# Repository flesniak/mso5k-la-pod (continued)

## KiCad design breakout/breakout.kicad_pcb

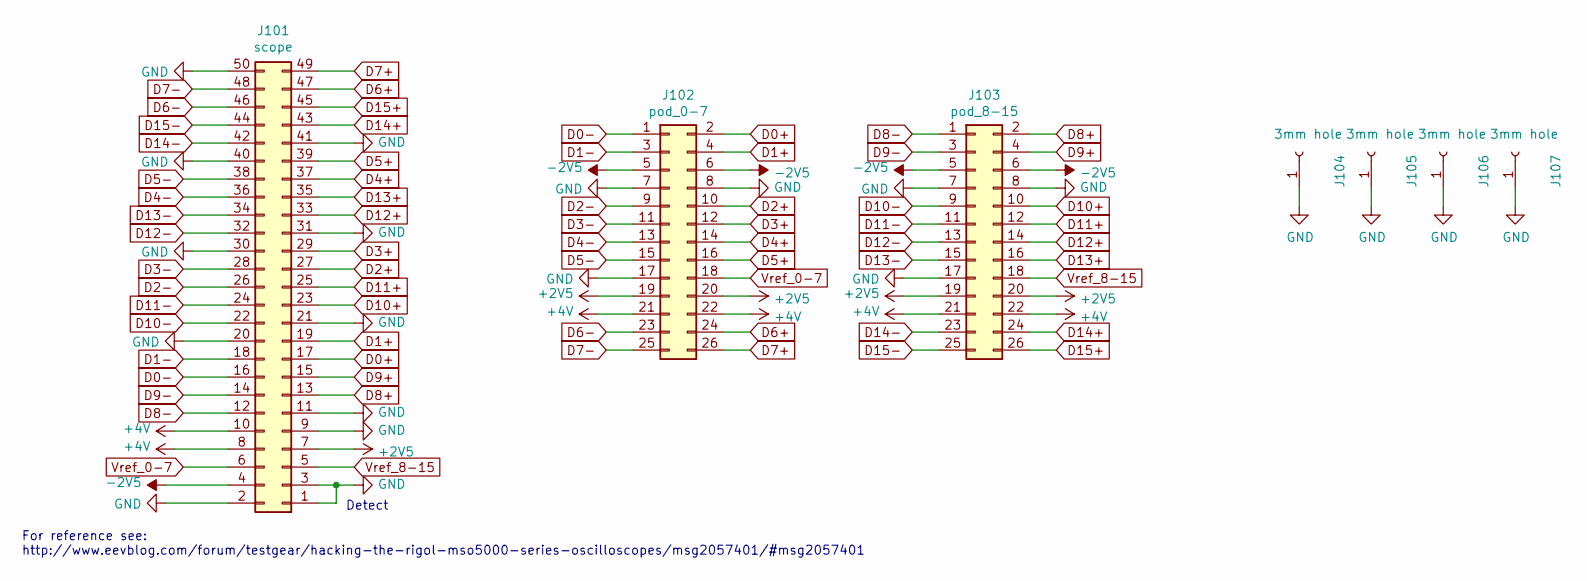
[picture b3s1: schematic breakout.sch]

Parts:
J101: scope; PinHeader_2x25_P2.54mm_Vertical
J102: pod_0-7; PinHeader_2x13_P1.27mm_Vertical_SMD
J103: pod_8-15; PinHeader_2x13_P1.27mm_Vertical_SMD
J104, J105, J106, J107: 3mm hole; 3mm

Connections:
+2V5: J101.7, J102.19, J102.20, J103.19, J103.20
+4V: J101.8, J101.10, J102.21, J102.22, J103.21, J103.22
-2V5: J101.4, J102.5, J102.6, J103.5, J103.6
D0+: J101.17, J102.2
D0-: J101.16, J102.1
D1+: J101.19, J102.4
D1-: J101.18, J102.3
D2+: J101.27, J102.10
D2-: J101.26, J102.9
D3+: J101.29, J102.12
D3-: J101.28, J102.11
D4+: J101.37, J102.14
D4-: J101.36, J102.13
D5+: J101.39, J102.16
D5-: J101.38, J102.15
D6+: J101.47, J102.24
D6-: J101.46, J102.23
D7+: J101.49, J102.26
D7-: J101.48, J102.25
D8+: J101.13, J103.2
D8-: J101.12, J103.1
D9+: J101.15, J103.4
D9-: J101.14, J103.3
D10+: J101.23, J103.10
D10-: J101.22, J103.9
D11+: J101.25, J103.12
D11-: J101.24, J103.11
D12+: J101.33, J103.14
D12-: J101.32, J103.13
D13+: J101.35, J103.16
D13-: J101.34, J103.15
D14+: J101.43, J103.24
D14-: J101.42, J103.23
D15+: J101.45, J103.26
D15-: J101.44, J103.25
GND: J101.1, J101.2, J101.3, J101.9, J101.11, J101.20, J101.21, J101.30, J101.31, J101.40, J101.41, J101.50, J102.7, J102.8, J102.17, J103.7, J103.8, J103.17, J104.1, J105.1, J106.1, J107.1
Vref_0-7: J101.6, J102.18
Vref_8-15: J101.5, J103.18

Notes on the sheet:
For reference see: http://www.eevblog.com/forum/testgear/hacking-the-rigol-mso5000-series-oscilloscopes/msg2057401/#msg2057401
Detect

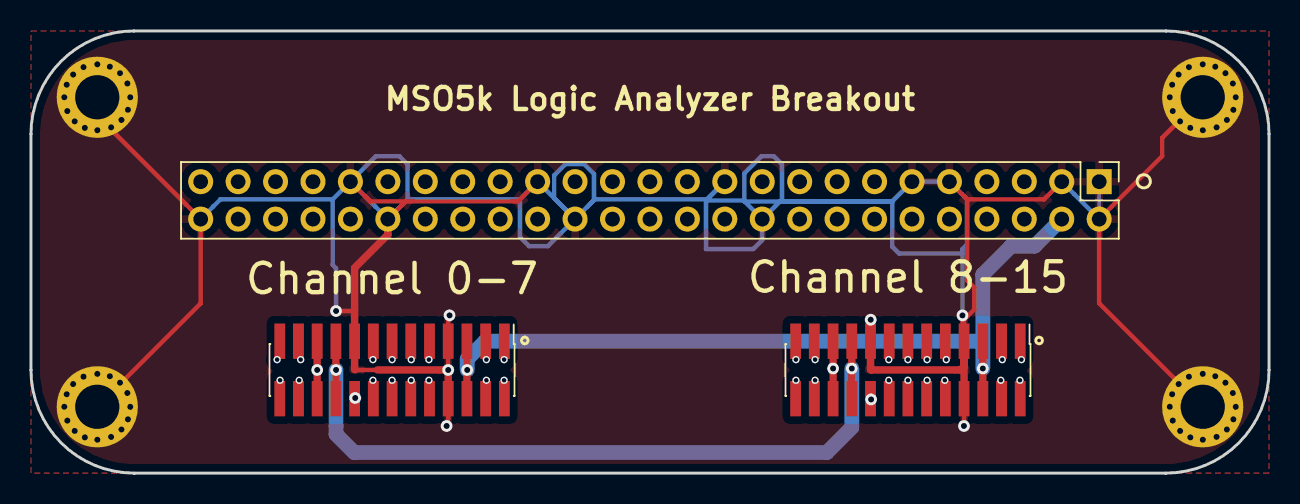
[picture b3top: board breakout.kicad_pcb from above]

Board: 4 copper layers, 84.0 x 30.0 mm, 7 parts (0 on the bottom side), 38 nets.

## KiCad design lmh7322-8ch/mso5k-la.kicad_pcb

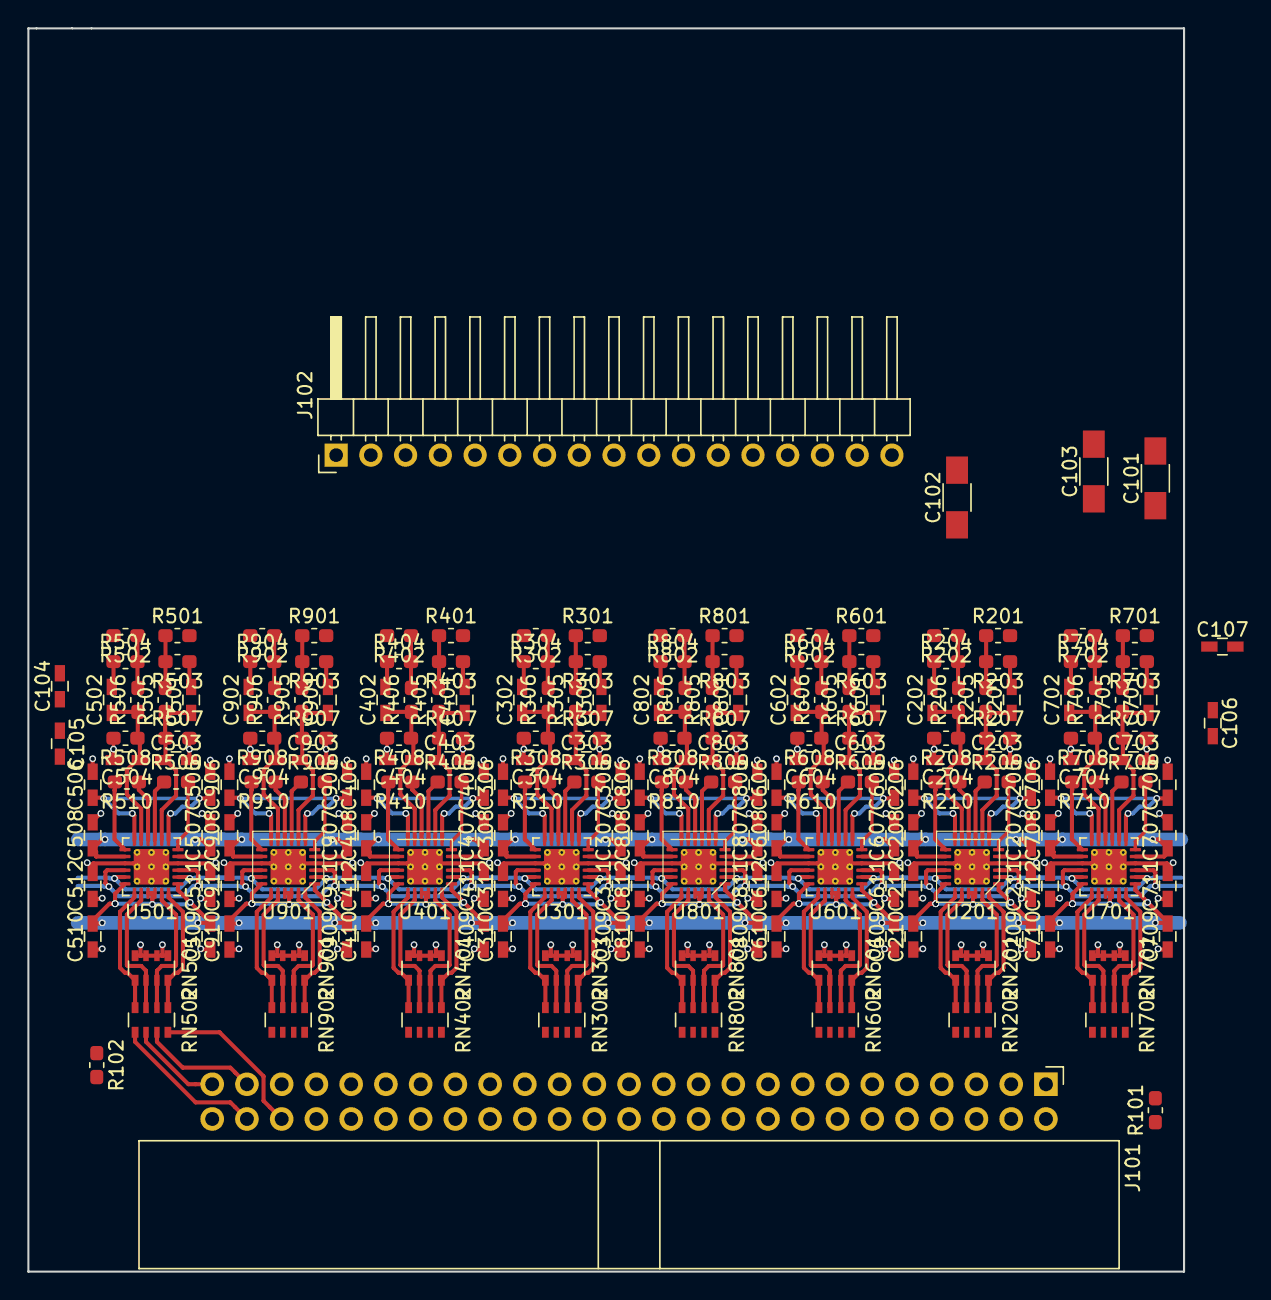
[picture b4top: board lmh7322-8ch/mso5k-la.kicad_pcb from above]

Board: 4 copper layers, 84.5 x 90.9 mm, 211 parts (0 on the bottom side), 168 nets.

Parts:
C101, C102, C103: 10uF; C_1206_HandSoldering
C104, C105, C106, C107, C207, C208, C209, C210, C211, C212, C307, C308, C309, C310, C311, C312, C407, C408, C409, C410, C411, C412, C507, C508, C509, C510, C511, C512, C607, C608, C609, C610, C611, C612, C707, C708, C709, C710, C711, C712, C807, C808, C809, C810, C811, C812, C907, C908, C909, C910, C911, C912: 100n; C_0603_HandSoldering
C201, C202, C301, C302, C401, C402, C501, C502, C601, C602, C701, C702, C801, C802, C901, C902: 3.3p; C_0603_HandSoldering
C203, C204, C303, C304, C403, C404, C503, C504, C603, C604, C703, C704, C803, C804, C903, C904: 27p; C_0603_HandSoldering
C205, C206, C305, C306, C405, C406, C505, C506, C605, C606, C705, C706, C805, C806, C905, C906: 10n; C_0603_HandSoldering
J101: output; IDC-Header_2x25_Pitch2.54mm_Angled
J102: input; PinHeader_1x17_P2.54mm_Horizontal
R101, R102: 1k; R_0603_1608Metric_Pad1.05x0.95mm_HandSolder
R201, R202, R301, R302, R401, R402, R501, R502, R601, R602, R701, R702, R801, R802, R901, R902: 300; R_0603_1608Metric_Pad1.05x0.95mm_HandSolder
R203, R204, R303, R304, R403, R404, R503, R504, R603, R604, R703, R704, R803, R804, R903, R904: 497; R_0603_1608Metric_Pad1.05x0.95mm_HandSolder
R205, R206, R305, R306, R405, R406, R505, R506, R605, R606, R705, R706, R805, R806, R905, R906: 90k8; R_0603_1608Metric_Pad1.05x0.95mm_HandSolder
R207, R208, R209, R210, R307, R308, R309, R310, R407, R408, R409, R410, R507, R508, R509, R510, R607, R608, R609, R610, R707, R708, R709, R710, R807, R808, R809, R810, R907, R908, R909, R910: 10k; R_0603_1608Metric_Pad1.05x0.95mm_HandSolder
RN201, RN301, RN401, RN501, RN601, RN701, RN801, RN901: 220; R_Array_Convex_4x0603
RN202, RN302, RN402, RN502, RN602, RN702, RN802, RN902: 49R9; R_Array_Convex_4x0603
U201, U301, U401, U501, U601, U701, U801, U901: lmh7322; QFN-24-1EP_4x4mm_P0.5mm_EP2.6x2.6mm_ThermalVias

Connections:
+2V5: C102.1, C209.2, C210.2, C309.2, C310.2, C409.2, C410.2, C509.2, C510.2, C609.2, C610.2, C709.2, C710.2, C809.2, C810.2, C909.2, C910.2, J101.7, R101.1, U201.1, U201.18, U201.21, U201.22, U301.1, U301.18, U301.21, U301.22, U401.1, U401.18, U401.21, U401.22, U501.1, U501.18, U501.21, U501.22, U601.1, U601.18, U601.21, U601.22, U701.1, U701.18, U701.21, U701.22, U801.1, U801.18, U801.21, U801.22, U901.1, U901.18, U901.21, U901.22
+4V: C101.1, C207.1, C208.1, C307.1, C308.1, C407.1, C408.1, C507.1, C508.1, C607.1, C608.1, C707.1, C708.1, C807.1, C808.1, C907.1, C908.1, J101.8, J101.10, U201.5, U201.14, U301.5, U301.14, U401.5, U401.14, U501.5, U501.14, U601.5, U601.14, U701.5, U701.14, U801.5, U801.14, U901.5, U901.14
-2V5: C103.1, C211.2, C212.2, C311.2, C312.2, C411.2, C412.2, C511.2, C512.2, C611.2, C612.2, C711.2, C712.2, C811.2, C812.2, C911.2, C912.2, J101.4, R102.1, U201.4, U201.15, U201.25, U301.4, U301.15, U301.25, U401.4, U401.15, U401.25, U501.4, U501.15, U501.25, U601.4, U601.15, U601.25, U701.4, U701.15, U701.25, U801.4, U801.15, U801.25, U901.4, U901.15, U901.25
D0: J101.17, RN202.7
D1: J101.19, RN202.6
D2: J101.27, RN302.7
D3: J101.29, RN302.6
D4: J101.37, RN402.7
D5: J101.39, RN402.6
D6: J101.47, RN502.7
D7: J101.49, RN502.6
D8: J101.13, RN702.7
D9: J101.15, RN702.6
D10: J101.23, RN602.7
D11: J101.25, RN602.6
D12: J101.33, RN802.7
D13: J101.35, RN802.6
D14: J101.43, RN902.7
D15: J101.45, RN902.6
GND: C101.2, C102.2, C103.2, C104.2, C105.2, C106.2, C107.2, C203.2, C204.2, C205.2, C206.2, C207.2, C208.2, C209.1, C210.1, C211.1, C212.1, C303.2, C304.2, C305.2, C306.2, C307.2, C308.2, C309.1, C310.1, C311.1, C312.1, C403.2, C404.2, C405.2, C406.2, C407.2, C408.2, C409.1, C410.1, C411.1, C412.1, C503.2, C504.2, C505.2, C506.2, C507.2, C508.2, C509.1, C510.1, C511.1, C512.1, C603.2, C604.2, C605.2, C606.2, C607.2, C608.2, C609.1, C610.1, C611.1, C612.1, C703.2, C704.2, C705.2, C706.2, C707.2, C708.2, C709.1, C710.1, C711.1, C712.1, C803.2, C804.2, C805.2, C806.2, C807.2, C808.2, C809.1, C810.1, C811.1, C812.1, C903.2, C904.2, C905.2, C906.2, C907.2, C908.2, C909.1, C910.1, C911.1, C912.1, J101.1, J101.2, J101.3, J101.9, J101.11, J101.20, J101.21, J101.30, J101.31, J101.40, J101.41, J101.50, J102.9, R207.2, R208.2, R307.2, R308.2, R407.2, R408.2, R507.2, R508.2, R607.2, R608.2, R707.2, R708.2, R807.2, R808.2, R907.2, R908.2, RN201.1, RN201.2, RN201.3, RN201.4, RN301.1, RN301.2, RN301.3, RN301.4, RN401.1, RN401.2, RN401.3, RN401.4, RN501.1, RN501.2, RN501.3, RN501.4, RN601.1, RN601.2, RN601.3, RN601.4, RN701.1, RN701.2, RN701.3, RN701.4, RN801.1, RN801.2, RN801.3, RN801.4, RN901.1, RN901.2, RN901.3, RN901.4
In0: J102.1, R201.2
In1: J102.2, R202.2
In2: J102.3, R301.2
In3: J102.4, R302.2
In4: J102.5, R401.2
In5: J102.6, R402.2
In6: J102.7, R501.2
In7: J102.8, R502.2
In8: J102.10, R701.2
In9: J102.11, R702.2
In10: J102.12, R601.2
In11: J102.13, R602.2
In12: J102.14, R801.2
In13: J102.15, R802.2
In14: J102.16, R901.2
In15: J102.17, R902.2
LE: R102.2, U201.2, U201.17, U301.2, U301.17, U401.2, U401.17, U501.2, U501.17, U601.2, U601.17, U701.2, U701.17, U801.2, U801.17, U901.2, U901.17
unnamed: C201.1, C203.1, R205.1, R207.1, U201.8
unnamed: C201.2, R203.1
unnamed: C202.1, C204.1, R206.1, R208.1, U201.11
unnamed: C202.2, R204.1
unnamed: C301.1, C303.1, R305.1, R307.1, U301.8
unnamed: C301.2, R303.1
unnamed: C302.1, C304.1, R306.1, R308.1, U301.11
unnamed: C302.2, R304.1
unnamed: C401.1, C403.1, R405.1, R407.1, U401.8
unnamed: C401.2, R403.1
unnamed: C402.1, C404.1, R406.1, R408.1, U401.11
unnamed: C402.2, R404.1
unnamed: C501.1, C503.1, R505.1, R507.1, U501.8
unnamed: C501.2, R503.1
unnamed: C502.1, C504.1, R506.1, R508.1, U501.11
unnamed: C502.2, R504.1
unnamed: C601.1, C603.1, R605.1, R607.1, U601.8
unnamed: C601.2, R603.1
unnamed: C602.1, C604.1, R606.1, R608.1, U601.11
unnamed: C602.2, R604.1
unnamed: C701.1, C703.1, R705.1, R707.1, U701.8
unnamed: C701.2, R703.1
unnamed: C702.1, C704.1, R706.1, R708.1, U701.11
unnamed: C702.2, R704.1
unnamed: C801.1, C803.1, R805.1, R807.1, U801.8
unnamed: C801.2, R803.1
unnamed: C802.1, C804.1, R806.1, R808.1, U801.11
unnamed: C802.2, R804.1
unnamed: C901.1, C903.1, R905.1, R907.1, U901.8
unnamed: C901.2, R903.1
unnamed: C902.1, C904.1, R906.1, R908.1, U901.11
unnamed: C902.2, R904.1
unnamed: R201.1, R203.2, R205.2
unnamed: R202.1, R204.2, R206.2
unnamed: R209.1, U201.9
unnamed: R209.2, U201.6
unnamed: R210.1, U201.10
unnamed: R210.2, U201.13
unnamed: R301.1, R303.2, R305.2
unnamed: R302.1, R304.2, R306.2
unnamed: R309.1, U301.9
unnamed: R309.2, U301.6
unnamed: R310.1, U301.10
unnamed: R310.2, U301.13
unnamed: R401.1, R403.2, R405.2
unnamed: R402.1, R404.2, R406.2
unnamed: R409.1, U401.9
unnamed: R409.2, U401.6
unnamed: R410.1, U401.10
unnamed: R410.2, U401.13
unnamed: R501.1, R503.2, R505.2
unnamed: R502.1, R504.2, R506.2
unnamed: R509.1, U501.9
unnamed: R509.2, U501.6
unnamed: R510.1, U501.10
unnamed: R510.2, U501.13
unnamed: R601.1, R603.2, R605.2
unnamed: R602.1, R604.2, R606.2
unnamed: R609.1, U601.9
unnamed: R609.2, U601.6
unnamed: R610.1, U601.10
unnamed: R610.2, U601.13
unnamed: R701.1, R703.2, R705.2
unnamed: R702.1, R704.2, R706.2
unnamed: R709.1, U701.9
unnamed: R709.2, U701.6
unnamed: R710.1, U701.10
unnamed: R710.2, U701.13
unnamed: R801.1, R803.2, R805.2
unnamed: R802.1, R804.2, R806.2
unnamed: R809.1, U801.9
unnamed: R809.2, U801.6
unnamed: R810.1, U801.10
unnamed: R810.2, U801.13
unnamed: R901.1, R903.2, R905.2
unnamed: R902.1, R904.2, R906.2
unnamed: R909.1, U901.9
unnamed: R909.2, U901.6
unnamed: R910.1, U901.10
unnamed: R910.2, U901.13
unnamed: RN201.5, RN202.4, U201.19
unnamed: RN201.6, RN202.3, U201.20
unnamed: RN201.7, RN202.2, U201.23
unnamed: RN201.8, RN202.1, U201.24
unnamed: RN301.5, RN302.4, U301.19
unnamed: RN301.6, RN302.3, U301.20
unnamed: RN301.7, RN302.2, U301.23
unnamed: RN301.8, RN302.1, U301.24
unnamed: RN401.5, RN402.4, U401.19
unnamed: RN401.6, RN402.3, U401.20
unnamed: RN401.7, RN402.2, U401.23
unnamed: RN401.8, RN402.1, U401.24
unnamed: RN501.5, RN502.4, U501.19
unnamed: RN501.6, RN502.3, U501.20
unnamed: RN501.7, RN502.2, U501.23
unnamed: RN501.8, RN502.1, U501.24
unnamed: RN601.5, RN602.4, U601.19
unnamed: RN601.6, RN602.3, U601.20
unnamed: RN601.7, RN602.2, U601.23
unnamed: RN601.8, RN602.1, U601.24
unnamed: RN701.5, RN702.4, U701.19
unnamed: RN701.6, RN702.3, U701.20
unnamed: RN701.7, RN702.2, U701.23
unnamed: RN701.8, RN702.1, U701.24
unnamed: RN801.5, RN802.4, U801.19
unnamed: RN801.6, RN802.3, U801.20
unnamed: RN801.7, RN802.2, U801.23
unnamed: RN801.8, RN802.1, U801.24
unnamed: RN901.5, RN902.4, U901.19
unnamed: RN901.6, RN902.3, U901.20
unnamed: RN901.7, RN902.2, U901.23
unnamed: RN901.8, RN902.1, U901.24
Vref_0-7: C104.1, C106.1, C205.1, C206.1, C305.1, C306.1, C405.1, C406.1, C505.1, C506.1, J101.6, U201.7, U201.12, U301.7, U301.12, U401.7, U401.12, U501.7, U501.12
Vref_8-15: C105.1, C107.1, C605.1, C606.1, C705.1, C706.1, C805.1, C806.1, C905.1, C906.1, J101.5, U601.7, U601.12, U701.7, U701.12, U801.7, U801.12, U901.7, U901.12
~D0: J101.16, RN202.8
~D1: J101.18, RN202.5
~D2: J101.26, RN302.8
~D3: J101.28, RN302.5
~D4: J101.36, RN402.8
~D5: J101.38, RN402.5
~D6: J101.46, RN502.8
~D7: J101.48, RN502.5
~D8: J101.12, RN702.8
~D9: J101.14, RN702.5
~D10: J101.22, RN602.8
~D11: J101.24, RN602.5
~D12: J101.32, RN802.8
~D13: J101.34, RN802.5
~D14: J101.42, RN902.8
~D15: J101.44, RN902.5
~LE: R101.2, U201.3, U201.16, U301.3, U301.16, U401.3, U401.16, U501.3, U501.16, U601.3, U601.16, U701.3, U701.16, U801.3, U801.16, U901.3, U901.16

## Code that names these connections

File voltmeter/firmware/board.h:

#pragma once

#include "avr8gpio.h"

/*
| Define         | AVR | Pin | Description |
|----------------|-----|-----|-------------|
| LED0           | PA0 | 13  | LED0        |
| LED1           | PA1 | 12  | LED1        |
| LED2           | PA2 | 11  | LED2        |
| LED3           | PA3 | 10  | LED3        |
| LED4           | PB0 | 2   | LED3        |
| CALIB          | PA6 | 7   | Calibration |
| VREF0          | PA5 | 8   | VrefA       |
| VREF1          | PA7 | 6   | VrefB       |
|                | PB3 | 4   | Reset       |
*/

#define LED0  GPA0
#define LED1  GPA1
#define LED2  GPA2
#define LED3  GPA3
#define LED4  GPB0
#define CALIB GPA6

#define VREF0 GPA5
#define VREF1 GPA7
#define VREF0_ADC 5
#define VREF1_ADC 7

//#define SOFTWARE_TX GPB0

// pullup for calibration input
#define DEFAULT_PORTA (_BV(PA6))

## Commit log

2019-01-17 Added readme
2019-01-17 Use resistor arrays in the outputs
2019-01-17 Minor cleanup
2019-01-18 Started playing around with the PCB layout
2019-01-18 Pre-clone
2019-01-21 Finished the 4-layer single-sided board
2019-01-24 Trying mass-edit of net names
2019-01-26 completed core layout of 16 channel lmh7324 design
2019-01-26 Forgot to add the 8 ch lmh7322 version
2019-01-26 Laid out the 8ch LMH7324 version and added a threshold display too
2019-01-26 Completed lmh7324 based 8ch pod with voltmeter
2019-01-26 Added the schematic of the 8ch lmh7324 based pod
2019-01-28 Golden revision before switching to SMD 1.27mm pitch header
2019-01-28 Switched to an SMD 1.27 mm pitch header for the cable to the scope to get a thinner uplink ribbon
2019-01-29 Added breakout
2019-01-30 Laid out 4 layer breakout board
2019-01-30 Switched to 0805 on the pod for the large bulk caps
2019-03-05 Added proper readme
2019-03-19 Added fixes for E1 and E2
2019-03-28 Cleaning up
2019-03-28 Started work on the volt meter code with a software uart to allow reading out the adc values, calling the adc causes everything to hang, though
2019-03-28 Added the datasheet for the controller
2019-03-30 Moved the ADC reading code to a free-running IRQ and bumped the clock frequency to 8 MHz to get better baud rate out of the software uart, might need to go back to 1MHz later
2019-03-31 Moved to interrupt driven ADC and charlieplexing
2019-04-07 Fixed LED voltages and calibration code
2019-04-09 Added an explanation of how the charlie plexing bits are stored
2019-04-12 Fixed startup animation so all LEDs are lit
2023-08-23 initial voltmeter for 16ch version
2023-09-17 firmware: final version with calibration for 16ch version
2023-09-17 lmh7324-16ch version schematics + board
2023-09-17 update readme once more
